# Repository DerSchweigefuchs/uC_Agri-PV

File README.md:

# uC_Agri-PV

**Low-Power Sensor Board for Agri-Photovoltaic Research**

A custom PCB designed for environmental monitoring in agricultural photovoltaic installations. Built around the STM32U5 ultra-low-power microcontroller with LoRaWAN connectivity and multiple sensor interfaces.

---

## Features

- **Ultra-Low Power Design** - Optimized for battery-powered field deployment with deep sleep support
- **LoRaWAN Connectivity** - Seeed LoRa-E5 module for long-range wireless data transmission
- **Multiple Sensor Interfaces** - ADC, I2C, OneWire, RS485 for various environmental sensors
- **Switchable Power Rails** - Individual MOSFET-controlled power for each sensor to minimize standby current
- **Local Data Storage** - MicroSD card slot for data logging
- **Flexible Power Input** - Battery, solar panel, or 5V DC input with integrated charging

---

## Hardware Specifications

| Component | Description |
|-----------|-------------|
| **MCU** | STM32U575ZIT6Q (ARM Cortex-M33, 160 MHz, ultra-low power) |
| **Wireless** | Seeed LoRa-E5 (STM32WLE5 + SX1262, LoRaWAN) |
| **WiFi/BLE** | ESP32-C6-WROOM-1-N8 (optional, MCU-controlled power) |
| **Storage** | MicroSD card slot (SDMMC 4-bit) |
| **Power** | Li-Ion battery (TP4056 charger), solar input, 5V DC |
| **RTC Backup** | SuperCap (FC0V104ZFTBR24) for timekeeping during power loss |

---

## Supported Sensors

| Sensor | Interface |
|--------|-----------|
| PAR (Photosynthetically Active Radiation) | RS485 |
| UV Radiation | ADC |
| Soil Moisture | ADC |
| Soil Temperature (DS18B20) | OneWire |
| Wind Speed (Anemometer) | ADC |
| BME680 (Temp, Humidity, Pressure, Gas) | I2C |
| Generic Analog (2 channels) | ADC |

All sensor power rails are individually switchable via GPIO-controlled MOSFETs for minimal deep sleep current consumption.

---

## Power Management

The board has flexible power options and MCU-controlled power switching for low-power operation.

For detailed information about power input selection, jumper settings, and GPIO power control see **[Power Control Documentation](POWER_CONTROL.md)**.

---

## Connectors Overview

### Debug & Programming

| Connector | Function |
|-----------|----------|
| X20 (DEBUG_STM) | 10-pin ARM Cortex SWD |
| JTAG_ESP | ESP32-C6 programming header |
| LORA JTAG | LoRa-E5 programming header |
| UART_ESP | ESP32 UART (RXD0, TXD0) |

### GPIO/UART Headers

| Connector | Signals |
|-----------|---------|
| X7 (GPIO STM) | STM32 GPIOs for UART debugging or other UART devices |
| X5 (GPIO STM) | Additional STM32 GPIOs |
| X4 (I2C STM) | I2C bus expansion |
| GPIO_ESP | ESP32-C6 GPIO breakout |

---

## Documentation

- **[Hardware Pinout](HARDWARE_PINOUT.md)** - GPIO assignments, sensor data pins, communication protocols
- **[Power Control](POWER_CONTROL.md)** - Power input selection, jumper settings, GPIO power switching
- **[Changelog](CHANGELOG.md)** - Version history and changes between revisions
- **[Interactive BOM](https://derschweigefuchs.github.io/uC_Agri-PV/bom/ibom.html)** - Component placement of materials

---

## Version History

| Version | Date | Description |
|---------|------|-------------|
| v2.0 | 2026-01-08 | Complete redesign with optimized power management |
| v1.3 | 2025-12-18 | Intermediate version (never produced) |
| v1.2 | 2025 | Initial release |

See **[CHANGELOG.md](CHANGELOG.md)** for detailed changes.

---

## License

This hardware design is part of a master's thesis of the University of Applied Science Karlsruhe of the project for Agri-PV research.

---

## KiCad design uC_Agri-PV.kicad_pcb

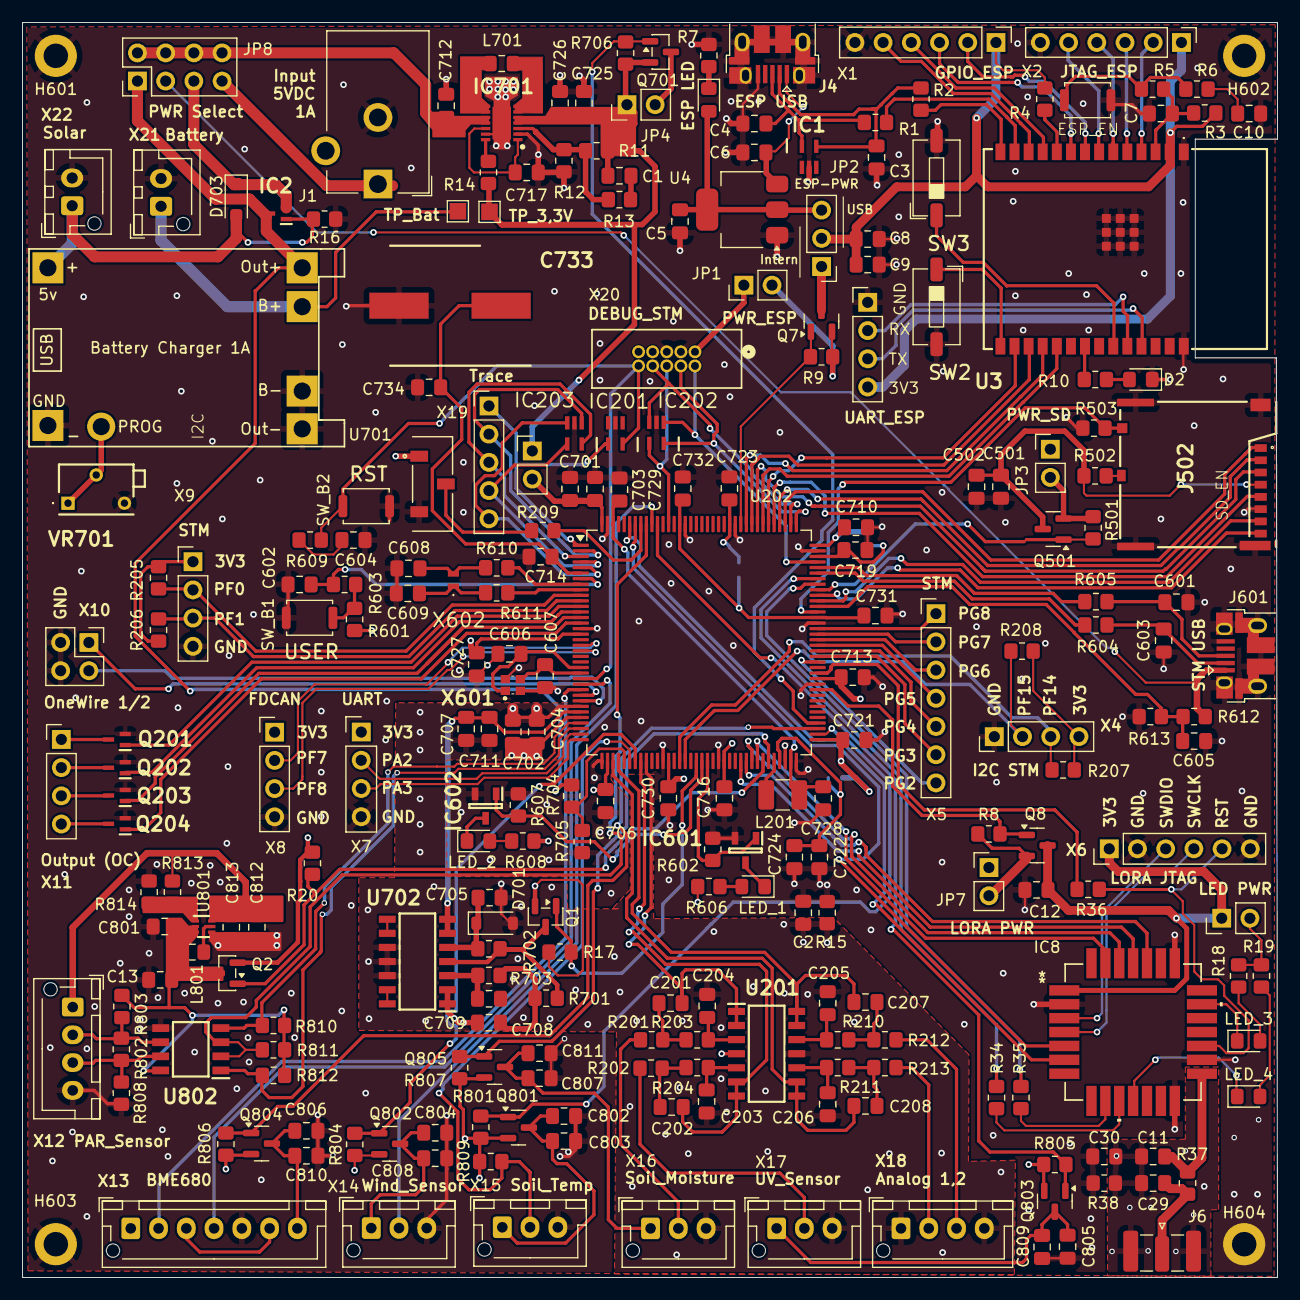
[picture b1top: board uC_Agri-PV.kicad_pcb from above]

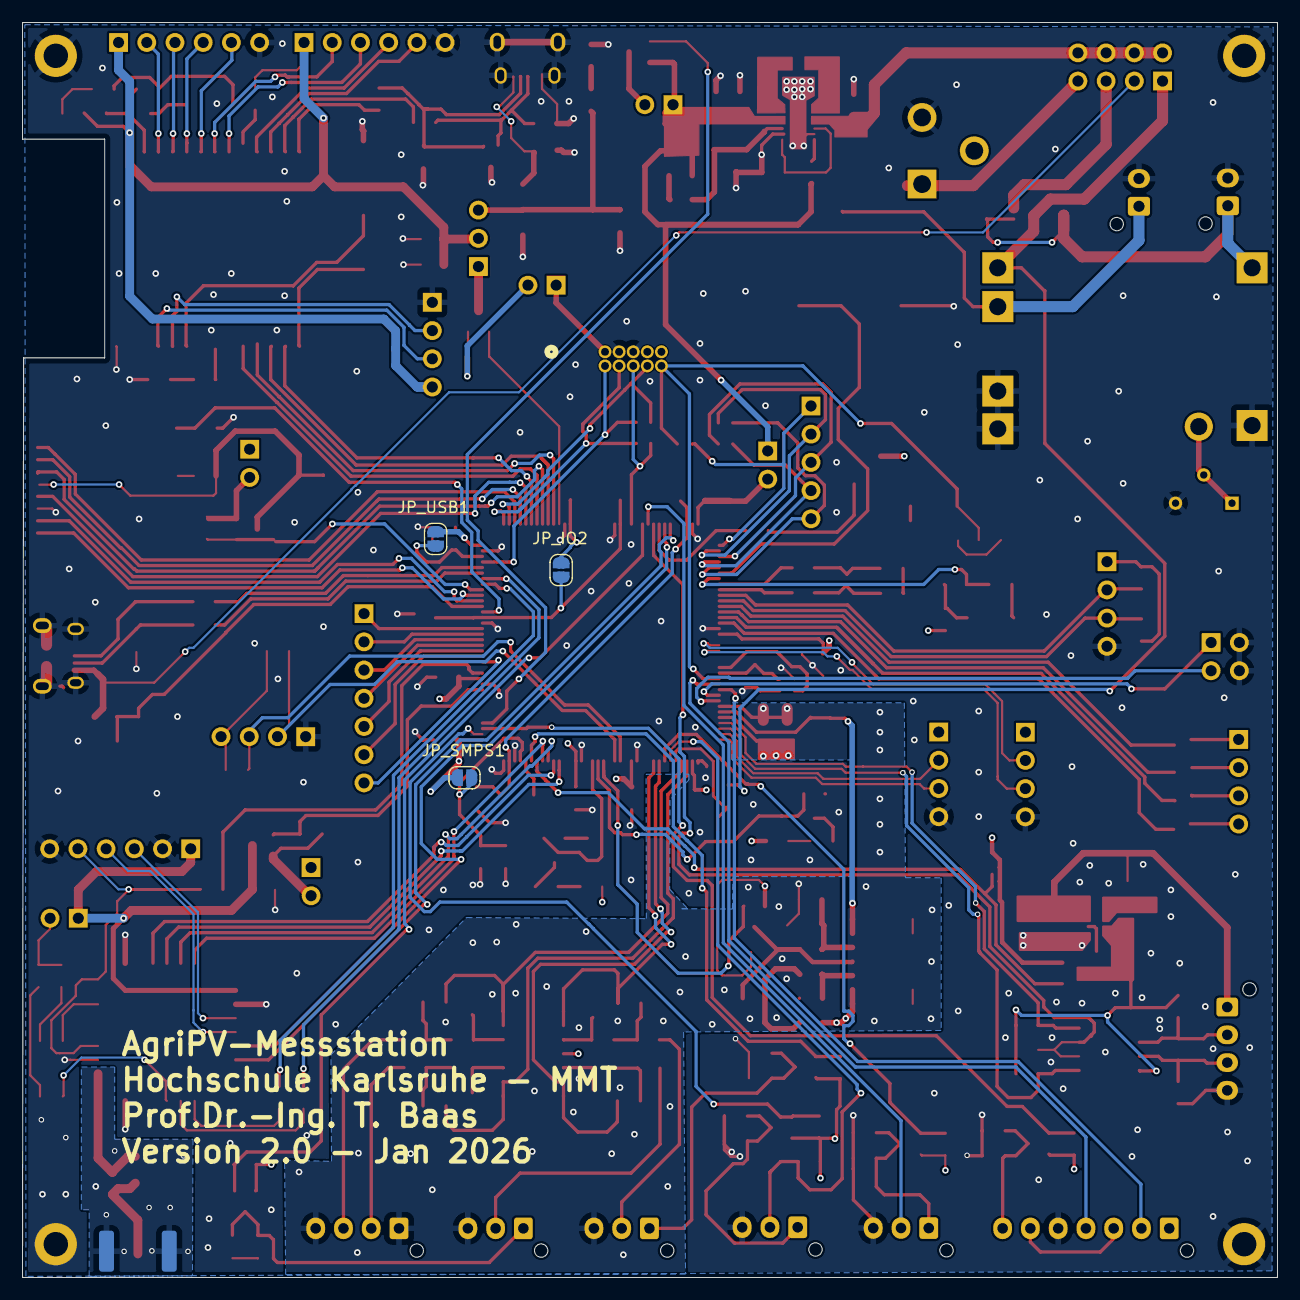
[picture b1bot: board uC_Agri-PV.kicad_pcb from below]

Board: 4 copper layers, 113.0 x 113.0 mm, 248 parts (3 on the bottom side), 203 nets.

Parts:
C1: 4.7pF; C_0805_2012Metric_Pad1.18x1.45mm_HandSolder
C2, C3, C4, C11, C29, C30, C601, C603: TBD; C_0805_2012Metric_Pad1.18x1.45mm_HandSolder
C5, C6, C8, C501, C602, C712, C725, C726, C801, C802, C804, C805, C806, C807, C812, C813: 22u; C_0805_2012Metric_Pad1.18x1.45mm_HandSolder
C7, C702, C705, C707, C714, C722: 1u; C_0805_2012Metric_Pad1.18x1.45mm_HandSolder
C9, C10, C13, C502, C604, C703, C704, C706, C710, C711, C713, C716, C717, C719, C721, C723, C724, C730, C731, C732, C734, C803, C808, C809, C810, C811: 100n; C_0805_2012Metric_Pad1.18x1.45mm_HandSolder
C12: 4,7uF; C_0805_2012Metric_Pad1.18x1.45mm_HandSolder
C201, C202, C207, C208, C708: 33n; C_0805_2012Metric_Pad1.18x1.45mm_HandSolder
C203, C204, C205, C206, C709: 15n; C_0805_2012Metric_Pad1.18x1.45mm_HandSolder
C605: 10p; C_0805_2012Metric_Pad1.18x1.45mm_HandSolder
C606, C607, C608, C609: 6.8pF; C_0805_2012Metric_Pad1.18x1.45mm_HandSolder
C701: 10u; C_0805_2012Metric_Pad1.18x1.45mm_HandSolder
C727: 4.7uF; C_0805_2012Metric_Pad1.18x1.45mm_HandSolder
C728, C729: 2.2u; C_0805_2012Metric_Pad1.18x1.45mm_HandSolder
C733: FC0V104ZFTBR24; CAPAE1080X550N
D2: LED; LED_0805_2012Metric_Pad1.15x1.40mm_HandSolder
D701: D_Zener; D_SOD-123
D703: D_Schottky; D_SOD-123F
H601, H602, H603, H604: MountingHole_Pad; MountingHole_2.2mm_M2_DIN965_Pad
IC1, IC201, IC202, IC203: ESDALC6V1W5; SOT65P210X110-5N
IC2: DMP1045U-7; SOT50P160X90-3N
IC8: 317990687; QFN_90687_SEE-M
IC601, IC602: MMS9013-L-TP; SOT95P237X125-3N
IC701: TPS63021DSJR; SON50P300X400X100-15N-D
J1: PJ-102B; BarrelJack_CUI_PJ-102AH_Horizontal
J4, J601: USB_B_Micro; USB_Micro-B_Amphenol_10103594-0001LF_Horizontal
J6: Conn_Coaxial; SMA_Samtec_SMA-J-P-H-ST-EM1_EdgeMount
J502: 503398-1892; 503398-1892-1
JP1, JP3, JP6, JP7: Conn_01x02_Pin; PinHeader_1x02_P2.54mm_Vertical
JP2: Jumper_3_Open; PinHeader_1x03_P2.54mm_Vertical
JP4, JP5: Jumper_2_Bridged; PinHeader_1x02_P2.54mm_Vertical
JP8: Conn_02x04_Odd_Even; PinHeader_2x04_P2.54mm_Vertical
JP_IO2: SolderJumper_2_Bridged; SolderJumper-2_P1.3mm_Open_RoundedPad1.0x1.5mm
JP_SMPS1: SolderJumper_2_Bridged; SolderJumper-2_P1.3mm_Open_RoundedPad1.0x1.5mm
JP_USB1: SolderJumper_2_Bridged; SolderJumper-2_P1.3mm_Open_RoundedPad1.0x1.5mm
L201: 2.2u; L_1210_3225Metric_Pad1.42x2.65mm_HandSolder
L701, L801: 1u; L_0805_2012Metric_Pad1.15x1.40mm_HandSolder
LED_1, LED_2, LED_3, LED_4, LED_5: LED; LED_0805_2012Metric_Pad1.15x1.40mm_HandSolder
Q1, Q2, Q7, Q8, Q501, Q701, Q801, Q802, Q803, Q804, Q805: IRLML6402; SOT-23
Q201, Q202, Q203, Q204: DMG1012T-13; SOT50P160X90-3N
R1, R2, R5, R11, R15, R37, R38, R502, R604, R605, R610, R611: 0R; R_0805_2012Metric_Pad1.20x1.40mm_HandSolder
R3, R16, R209, R810, R811, R812: 10k; R_0805_2012Metric_Pad1.20x1.40mm_HandSolder
R4, R8, R9, R17, R20, R501, R503, R601, R602, R607, R706, R801, R804, R805, R806, R807, R814: 100k; R_0805_2012Metric_Pad1.20x1.40mm_HandSolder
R6, R7, R10, R18, R19, R201, R202, R212, R213, R603, R606, R608, R609, R701, R702: 1k; R_0805_2012Metric_Pad1.20x1.40mm_HandSolder
R12: 180k; R_0805_2012Metric_Pad1.20x1.40mm_HandSolder
R13: 68k; R_0805_2012Metric_Pad1.20x1.40mm_HandSolder
R14: 1M; R_0805_2012Metric_Pad1.20x1.40mm_HandSolder
R34, R35, R36: 22; R_0805_2012Metric_Pad1.20x1.40mm_HandSolder
R203, R204, R210, R211, R703: 2k; R_0805_2012Metric_Pad1.20x1.40mm_HandSolder
R205, R206, R207, R208: 2k2; R_0805_2012Metric_Pad1.20x1.40mm_HandSolder
R612, R704, R705: 330k; R_0805_2012Metric_Pad1.20x1.40mm_HandSolder
R613: 49k9; R_0805_2012Metric_Pad1.20x1.40mm_HandSolder
R802: 120; R_0805_2012Metric_Pad1.20x1.40mm_HandSolder
R803, R808: 20k; R_0805_2012Metric_Pad1.20x1.40mm_HandSolder
R809: 4,7k; R_0805_2012Metric_Pad1.20x1.40mm_HandSolder
R813: 732k; R_0805_2012Metric_Pad1.20x1.40mm_HandSolder
SW1: SW_SPDT; SW_JS102011JCQN
SW2, SW3: SW_DIP_x01; SW_DIP_SPSTx01_Slide_6.7x4.1mm_W6.73mm_P2.54mm_LowProfile_J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
SW_B1, SW_B2, SW_B3: SW_Push; SW_Push_SPST_NO_Alps_SKRK
TP_3,3V1: TestPoint; TestPoint_Pad_1.5x1.5mm
TP_Battery1: TestPoint; TestPoint_Pad_1.5x1.5mm
U3: ESP32-C6-WROOM-1-N8; ESP32C6WROOM1N8
U4: AMS1117-3.3; SOT-223-3_TabPin2
U201, U702: TLV9304IDR; SOIC127P600X175-14N
U202: STM32U575ZIT6Q; LQFP-144_20x20mm_P0.5mm
U701: TP4056-18650-2
U801: TPS61023DRLR; DRL0006A
U802: ISL83078EIBZA; SOIC127P600X175-8N
VR701: 3266X-1-203LF; 3266X1203LF
X1, X2, X6: Conn_01x06_Pin; PinHeader_1x06_P2.54mm_Vertical
X3, X4, X7, X8, X9, X11: Conn_01x04_Pin; PinHeader_1x04_P2.54mm_Vertical
X5: Conn_01x07_Pin; PinHeader_1x07_P2.54mm_Vertical
X10: Conn_02x02_Counter_Clockwise; PinHeader_2x02_P2.54mm_Vertical
X12, X18: Conn_01x04_Pin; JST_XH_B4B-XH-AM_1x04_P2.50mm_Vertical
X13: Conn_01x07_Pin; JST_XH_B7B-XH-AM_1x07_P2.50mm_Vertical
X14, X15, X16, X17: Conn_01x03_Pin; JST_XH_B3B-XH-AM_1x03_P2.50mm_Vertical
X19: Conn_01x05_Pin; PinHeader_1x05_P2.54mm_Vertical
X20: 3220-10-0100-00; CONN_3220-10-0100-00_CNC
X21, X22: Conn_01x02_Pin; JST_XH_B2B-XH-AM_1x02_P2.50mm_Vertical
X601: XTAL_4_PINS; NX2016SA32MEXS00ACS06465
X602: XTAL_2_PINS; NX1610SA32768000kHz

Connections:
+3.3V: JP1.1, JP3.1, JP4.2 (B), JP7.1, Q1.2 (S), Q2.2 (S), Q701.3 (D), Q801.2 (S), Q802.2 (S), Q803.2 (S), Q804.2 (S), Q805.2 (S), R17.2, R20.2, R205.2, R206.2, R207.2, R208.2, R601.2, R606.1, R608.1, R801.1, R804.2, R805.2, R806.2, R807.2, R809.2, SW1.1 (A), X4.4, X7.1, X8.1, X9.1, X20.1
+BATT: TP_Battery1.1, U701.5 (B+), X21.1
/ESP32-C6-WROOM-1-N8/3V3_ESP: C8.2, C9.2, JP2.2 (C), R3.1, R4.2, U3.2 (3V3), X1.1, X2.1, X3.4
/ESP32-C6-WROOM-1-N8/EN: C7.2, R3.2, R5.2, U3.3 (EN)
/ESP32-C6-WROOM-1-N8/ESP32_EN: Q7.1 (G), R9.1, U202.119 (PD5)
/ESP32-C6-WROOM-1-N8/ESP32_MISO: U3.17 (IO19), U202.117 (PD3)
/ESP32-C6-WROOM-1-N8/ESP32_MOSI: U3.18 (IO20), U202.118 (PD4)
/ESP32-C6-WROOM-1-N8/ESP32_NSS: U3.16 (IO18), U202.114 (PD0)
/ESP32-C6-WROOM-1-N8/ESP32_SCK: U3.19 (IO21), U202.115 (PD1)
/ESP32-C6-WROOM-1-N8/IO10: U3.11 (IO10), X1.4
/ESP32-C6-WROOM-1-N8/IO11: U3.12 (IO11), X1.5
/ESP32-C6-WROOM-1-N8/VBus_ESP32: C6.2, J4.1 (VBUS), U4.3 (VI)
/IO and mounting holes/LED1: IC601.1 (B), R602.2, U202.56 (PE8)
/IO and mounting holes/LED2: IC602.1 (B), R607.2, U202.55 (PE7)
/IO and mounting holes/PC14-OSC32_IN: R610.1, U202.8 (PC14)
/IO and mounting holes/PC15-OSC32_OUT: R611.1, U202.9 (PC15)
/IO and mounting holes/PH0-OSC_IN: C606.2, U202.23 (PH0), X601.1
/IO and mounting holes/PH1-OSC_OUT: C607.2, U202.24 (PH1), X601.3
/IO and mounting holes/USB_1_D+: C601.2, J601.3 (D+), R605.1
/IO and mounting holes/USB_1_D-: C603.2, J601.2 (D-), R604.1
/IO and mounting holes/USB_D+: R605.2, U202.104 (PA12)
/IO and mounting holes/USB_D-: R604.2, U202.103 (PA11)
/IO and mounting holes/User_Button: C602.2, R603.1, U202.7 (PC13)
/IO and mounting holes/VBUS: J601.1 (VBUS), JP8.3, R612.1
/IO and mounting holes/VBUS_SENSE: C605.2, R612.2, R613.1, U202.97 (PC7)
/LoRa-E5/3V3_LORA: C12.2, IC8.1 (VCC), JP6.1, Q8.3 (D), X6.1
/LoRa-E5/LoRa_EN: Q8.1 (G), R8.1, U202.82 (PD13)
/LoRa-E5/MISO_LoRa: IC8.26 (PB14), U202.64 (PE14)
/LoRa-E5/MOSI_LoRa: IC8.27 (PA10), U202.65 (PE15)
/LoRa-E5/NRST2: R36.2, U202.85 (PD14)
/LoRa-E5/NSS_LoRa: IC8.25 (PB9), U202.62 (PE12)
/LoRa-E5/SCK_LoRa: IC8.24 (PB13), U202.63 (PE13)
/LoRa-E5/SCL_LoRa: IC8.5 (PB15), U202.138 (PB8)
/LoRa-E5/SDA_LoRa: IC8.6 (PA15), U202.139 (PB9)
/LoRa-E5/UART_RX: R35.1, U202.102 (PA10)
/LoRa-E5/UART_TX: R34.1, U202.101 (PA9)
/Micro SD-Card Reader 503398-1892/3V3_SD: C501.2, C502.2, J502.4 (VDD), Q501.3 (D), R502.2
/Micro SD-Card Reader 503398-1892/SD_CLK: J502.5 (CLK), U202.113 (PC12)
/Micro SD-Card Reader 503398-1892/SD_CMD: J502.3 (CMD), U202.116 (PD2)
/Micro SD-Card Reader 503398-1892/SD_DAT0: J502.7 (DAT0), U202.98 (PC8)
/Micro SD-Card Reader 503398-1892/SD_DAT1: J502.8 (DAT1), U202.99 (PC9)
/Micro SD-Card Reader 503398-1892/SD_DAT2: J502.1 (DAT2), U202.111 (PC10)
/Micro SD-Card Reader 503398-1892/SD_DAT3: J502.2 (CD/DAT3), U202.112 (PC11)
/Micro SD-Card Reader 503398-1892/SD_Detect: J502.9 (DETECT_LEVER), R503.1, U202.96 (PC6)
/Micro SD-Card Reader 503398-1892/SD_EN: Q501.1 (G), R501.1, U202.100 (PA8)
/Power Supply/3V3_EN: Q701.1 (G), R706.1, U202.76 (PB15)
/Power Supply/3V3_OPV_EN: Q1.1 (G), R17.1, U202.54 (PG1)
/Power Supply/3V3_OPV_PWR: Q1.3 (D), R701.1, R702.2, U702.4 (V+)
/Power Supply/3V3_VDD: C1.1, C725.1, C726.1, IC701.4 (VOUT_1), IC701.5 (VOUT_2), JP4.1 (A), JP5.1 (A), Q701.2 (S), R11.2, R14.1, R706.2, TP_3,3V1.1
/Power Supply/VBat: C714.1, C733.1 (+), C734.1, U202.6 (VBAT)
/Power Supply/VBat_meas: R704.2, R705.1, U202.41 (PA6)
/Power Supply/VRefP: C707.1, C711.1, U202.31 (VREF+), U702.6 (IN_B), U702.7 (OUT_B)
/Power Supply/Vdd_Bat: IC2.3 (D), JP8.1, R704.1, U701.3 (Out+)
/Power Supply/Vdd_Ext: D703.1 (K), IC2.2 (S), JP8.5
/Power Supply/Vdd_IO2: C731.1, C732.1, JP_IO2.2 (B), U202.95 (VDDIO2), U202.130 (VDDIO2)
/Power Supply/Vdd_MCU: C701.1, C703.1, C706.1, C710.1, C713.1, C716.1, C721.1, C723.1, C727.1, C730.1, JP5.2 (B), JP_IO2.1 (A), JP_SMPS1.1 (A), JP_USB1.1 (A), U202.17 (VDD), U202.38 (VDD), U202.49 (VDD), U202.59 (VDD), U202.73 (VDD), U202.84 (VDD), U202.108 (VDD), U202.121 (VDD), U202.144 (VDD)
/Power Supply/Vdd_SMPS: C722.1, C724.1, JP_SMPS1.2 (B), U202.69 (VDDSMPS)
/Power Supply/Vdd_USB: C719.1, JP_USB1.2 (B), U202.106 (VDDUSB)
/STM32U575ZIT6Q/ADC4_IN9: C208.2, U201.8 (OUT_C), U201.9 (IN_C), U202.39 (PA4)
/STM32U575ZIT6Q/ADC4_IN10: C207.2, U201.13 (IN_D), U201.14 (OUT_D), U202.40 (PA5)
/STM32U575ZIT6Q/BME_EN: Q804.1 (G), R806.1, U202.75 (PB14)
/STM32U575ZIT6Q/DEBUG_JTCK: IC202.5 (I/04), U202.109 (PA14), X20.4
/STM32U575ZIT6Q/DEBUG_JTDI: IC202.3 (I/02), U202.110 (PA15), X20.8
/STM32U575ZIT6Q/DEBUG_JTDO: IC202.4 (I/03), U202.132 (PB3), X20.6
/STM32U575ZIT6Q/DEBUG_JTMS: IC202.1 (I/01), U202.105 (PA13), X20.2
/STM32U575ZIT6Q/DE/RE: R811.1, U202.136 (PB7), U802.2 (*RE), U802.3 (DE)
/STM32U575ZIT6Q/I2C3_SCL: U202.26 (PC0), X13.4
/STM32U575ZIT6Q/I2C3_SDA: U202.27 (PC1), X13.2
/STM32U575ZIT6Q/NRST: IC201.5 (I/04), R609.2, SW_B2.2, U202.25 (NRST), X20.10
/STM32U575ZIT6Q/PAR_EN: Q2.1 (G), R20.1, U202.66 (PB10)
/STM32U575ZIT6Q/Signal_UV_radiation: R202.1, X17.2
/STM32U575ZIT6Q/Signal_soil_moisture: R201.1, X16.2
/STM32U575ZIT6Q/Signal_wind_velocity: U202.135 (PB6), X14.2
/STM32U575ZIT6Q/SoilMoist_EN: Q805.1 (G), R807.1, U202.67 (PB11)
/STM32U575ZIT6Q/SoilTemp_EN: Q801.1 (G), R801.2, U202.74 (PB13)
/STM32U575ZIT6Q/Soil_Moisture: C201.1, U201.1 (OUT_A), U201.2 (IN_A), U202.45 (PB2)
/STM32U575ZIT6Q/UART4_RX: R812.1, U202.34 (PA1), U802.1 (RO)
/STM32U575ZIT6Q/UART4_TX: R810.1, U202.33 (PA0), U802.4 (DI)
/STM32U575ZIT6Q/USART2_ONEWIRE: R809.1, U202.42 (PA7), X15.2
/STM32U575ZIT6Q/UV_EN: Q803.1 (G), R805.1, U202.134 (PB5)
/STM32U575ZIT6Q/UV_Radiation: C202.1, U201.6 (IN_B), U201.7 (OUT_B), U202.44 (PB1)
/STM32U575ZIT6Q/Vdd_11: C728.1, C729.1, L201.1, U202.71 (VDD11), U202.142 (VDD11)
/STM32U575ZIT6Q/Wind_EN: Q802.1 (G), R804.1, U202.43 (PB0)
/Sensors/3V3_PAR: C13.2, C801.2, L801.1, Q2.3 (D), R803.1, R810.2, R811.2, R812.2, U801.2 (EN), U801.3 (VIN), U802.8 (VCC)
/Sensors/5V: C812.2, C813.2, R813.1, U801.6 (VOUT), X12.1
GND: C2.2, C3.1, C4.1, C5.1, C6.1, C7.1, C8.1, C9.1, C10.1, C12.1, C13.1, C30.2, C501.1, C502.1, C601.1, C602.1, C603.1, C604.1, C605.1, C606.1, C607.1, C608.1, C609.1, C701.2, C703.2, C706.2, C710.2, C712.2, C713.2, C714.2, C716.2, C717.2, C719.2, C721.2, C722.2, C723.2, C724.2, C725.2, C726.2, C727.2, C728.2, C729.2, C730.2, C731.2, C732.2, C733.2 (-), C734.2, C801.1, C802.1, C803.1, C804.1, C805.1, C806.1, C807.1, C808.1, C809.1, C810.1, C811.1, C812.1, C813.1, D2.1 (K), H601.1, H602.1, H603.1, H604.1, IC1.2 (GND), IC8.2 (GND_1), IC8.14 (GND_2), IC8.16 (GND_3), IC8.22 (GND_4), IC201.2 (GND), IC202.2 (GND), IC203.2 (GND), IC601.2 (E), IC602.2 (E), IC701.2 (GND), IC701.13 (PS/SYNC), IC701.15 (EP), J1.2, J4.5 (GND), J4.6 (Shield), J502.6 (VSS), J502.11, J502.12, J502.13, J502.14, J601.5 (GND), J601.6 (Shield), Q201.2 (S), Q202.2 (S), Q203.2 (S), Q204.2 (S), R7.2, R12.1, R15.2, R16.1, R38.2, R503.2, R602.1, R607.1, R613.2, R705.2, R808.2, R814.2, SW1.3 (C), SW2.2, SW3.2, SW_B1.2, SW_B2.1, SW_B3.1, U3.1 (GND), U3.28 (GND), U3.29 (GND), U3.30 (GND), U3.31 (GND), U3.32 (GND), U3.33 (GND), U3.34 (GND), U3.35 (GND), U3.36 (GND), U3.37 (GND), U4.1 (GND), U202.16 (VSS), U202.37 (VSS), U202.48 (VSS), U202.58 (VSS), U202.70 (VSSSMPS), U202.72 (VSS), U202.83 (VSS), U202.94 (VSS), U202.107 (VSS), U202.120 (VSS), U202.129 (VSS), U202.143 (VSS), U701.2 (GND), U701.4 (Out-), U701.6 (B-), U801.4 (GND), U802.5 (GND), VR701.3 (CW), X1.6, X2.6, X3.1, X4.1, X6.2, X6.6, X7.4, X8.4, X9.4, X10.3, X10.4, X12.4, X13.5, X14.3, X15.3, X20.3, X20.5, X21.2, X22.2, X601.2, X601.4
GND1: C11.1, C29.1, C30.1, J6.2 (Ext), R38.1
GNDA: C2.1, C203.2, C204.1, C205.1, C206.2, C702.2, C704.2, C705.2, C707.2, C709.2, C711.2, D701.2 (A), R15.1, U201.11 (V), U202.30 (VSSA), U702.10 (+IN_C), U702.11 (V), U702.12 (+IN_D), X16.3, X17.3, X18.1, X18.4
unnamed: C1.2, R13.2
unnamed: C10.2, R6.1
unnamed: C201.2, R201.2, R203.1
unnamed: C202.2, R202.2, R204.1
unnamed: C207.1, R210.2, R212.1
unnamed: C208.1, R211.2, R213.1
unnamed: C604.2, R609.1
unnamed: C708.1, R701.2, R703.1
unnamed: D2.2 (A), R10.1
unnamed: C705.1, D701.1 (K), R702.1, U702.5 (+IN_B)
unnamed: D703.2 (A), IC2.1 (G), R16.2, U701.1 (5v), X22.1
unnamed: C3.2, IC1.4 (I/03), J4.2 (D-), R2.2
unnamed: C4.2, IC1.5 (I/04), J4.3 (D+), R1.2
unnamed: IC8.3 (PA13), X6.3
unnamed: IC8.4 (PA14), X6.4
unnamed: IC8.11 (PB5), LED_4.1 (K)
unnamed: IC8.10 (PB6), R35.2
unnamed: IC8.9 (PB7), R34.2
unnamed: IC8.20 (PB10), LED_3.1 (K)
unnamed: C11.2, IC8.15 (RFIO), R37.1
unnamed: IC8.17 (RST), R36.1, X6.5
unnamed: IC201.4 (I/03), U202.1 (PE2), X19.1
unnamed: IC203.1 (I/01), U202.2 (PE3), X19.2
unnamed: IC203.3 (I/02), U202.5 (PE6), X19.5
unnamed: IC203.4 (I/03), U202.4 (PE5), X19.4
unnamed: IC203.5 (I/04), U202.3 (PE4), X19.3
unnamed: IC601.3 (C), LED_1.1 (K)
unnamed: IC602.3 (C), LED_2.1 (K)
unnamed: C717.1, IC701.1 (VINA), IC701.12 (EN)
unnamed: IC701.3 (FB), R11.1, R12.2, R13.1
unnamed: IC701.8 (L1_1), IC701.9 (L1_2), L701.1
unnamed: IC701.6 (L2_1), IC701.7 (L2_2), L701.2
unnamed: IC701.14 (PG), R14.2
unnamed: C712.1, IC701.10 (VIN_1), IC701.11 (VIN_2), JP8.2, JP8.4, JP8.6, JP8.8
unnamed: C29.2, J6.1 (In), R37.2
unnamed: J502.10 (DETECT_SWITCH), R502.1
unnamed: JP1.2, Q7.2 (S), R9.2
unnamed: JP2.1 (A), Q7.3 (D)
unnamed: C5.2, JP2.3 (B), LED_5.2 (A), U4.2 (VO)
unnamed: JP3.2, Q501.2 (S), R501.2
unnamed: JP6.2, R18.1, R19.1
unnamed: JP7.2, Q8.2 (S), R8.2
unnamed: J1.1, JP8.7
unnamed: LED_1.2 (A), R606.2
unnamed: LED_2.2 (A), R608.2
unnamed: LED_3.2 (A), R18.2
unnamed: LED_4.2 (A), R19.2
unnamed: LED_5.1 (K), R7.1
unnamed: Q201.3 (D), X11.1
unnamed: Q201.1 (G), U202.12 (PF2)
unnamed: Q202.3 (D), X11.2
unnamed: Q202.1 (G), U202.13 (PF3)
unnamed: Q203.3 (D), X11.3
unnamed: Q203.1 (G), U202.14 (PF4)
unnamed: Q204.3 (D), X11.4
unnamed: Q204.1 (G), U202.15 (PF5)
unnamed: C802.2, C803.2, Q801.3 (D), X15.1
unnamed: C804.2, C808.2, Q802.3 (D), X14.1
unnamed: C805.2, C809.2, Q803.3 (D), X17.1
unnamed: C806.2, C810.2, Q804.3 (D), X13.7
unnamed: C807.2, C811.2, Q805.3 (D), X16.1
unnamed: R5.1, R6.2, SW_B3.2
unnamed: R601.1, R603.2, SW_B1.1
unnamed: R209.1, SW1.2 (B)
unnamed: U3.8 (IO0), X1.2
unnamed: U3.9 (IO1), X1.3
unnamed: U3.4 (IO4), X2.2
unnamed: U3.5 (IO5), X2.3
unnamed: U3.6 (IO6), X2.4
unnamed: U3.7 (IO7), X2.5
unnamed: R4.1, U3.10 (IO8)
unnamed: SW2.1, U3.15 (IO9)
unnamed: R1.1, U3.13 (IO12)
unnamed: R2.1, U3.14 (IO13)
unnamed: SW3.1, U3.23 (IO15)
unnamed: R10.2, U3.21 (IO23)
unnamed: U3.24 (RXD0/GPIO17), X3.2
unnamed: U3.25 (TXD0/GPIO16), X3.3
unnamed: C204.2, R203.2, U201.3 (+IN_A)
unnamed: C203.1, R204.2, U201.5 (+IN_B)
unnamed: C206.1, R211.1, U201.10 (+IN_C)
unnamed: C205.2, R210.1, U201.12 (+IN_D)
unnamed: U202.35 (PA2), X7.2
unnamed: U202.36 (PA3), X7.3
unnamed: U202.28 (PC2), X10.1
unnamed: U202.29 (PC3), X10.2
unnamed: R205.1, U202.10 (PF0), X9.2
unnamed: R206.1, U202.11 (PF1), X9.3
unnamed: U202.19 (PF7), X8.2
unnamed: U202.20 (PF8), X8.3
unnamed: R207.1, U202.51 (PF14), X4.3
unnamed: R208.1, U202.52 (PF15), X4.2
unnamed: U202.87 (PG2), X5.7
unnamed: U202.88 (PG3), X5.6
unnamed: U202.89 (PG4), X5.5
unnamed: U202.90 (PG5), X5.4
unnamed: U202.91 (PG6), X5.3
unnamed: U202.92 (PG7), X5.2
unnamed: U202.93 (PG8), X5.1
unnamed: R209.2, U202.137 (PH3)
unnamed: L201.2, U202.68 (VLXSMPS)
unnamed: U701.7 (PROG), VR701.1 (CCW), VR701.2 (WIPER)
unnamed: C709.1, R703.2, U702.3 (+IN_A)
unnamed: U702.8 (OUT_C), U702.9 (IN_C)
unnamed: U702.13 (IN_D), U702.14 (OUT_D)
unnamed: R813.2, R814.1, U801.1 (FB)
unnamed: L801.2, U801.5 (SW)
unnamed: R802.2, R803.2, U802.6 (A/Y), X12.2
unnamed: R802.1, R808.1, U802.7 (B/Z), X12.3
unnamed: X13.3, X13.6
unnamed: R213.2, X18.2
unnamed: R212.2, X18.3
unnamed: C609.2, R611.2, X602.1 (X1)
unnamed: C608.2, R610.2, X602.2 (X2)
VDDA: C702.1, C704.1, C708.2, U201.4 (V+), U202.32 (VDDA), U702.1 (OUT_A), U702.2 (IN_A)
